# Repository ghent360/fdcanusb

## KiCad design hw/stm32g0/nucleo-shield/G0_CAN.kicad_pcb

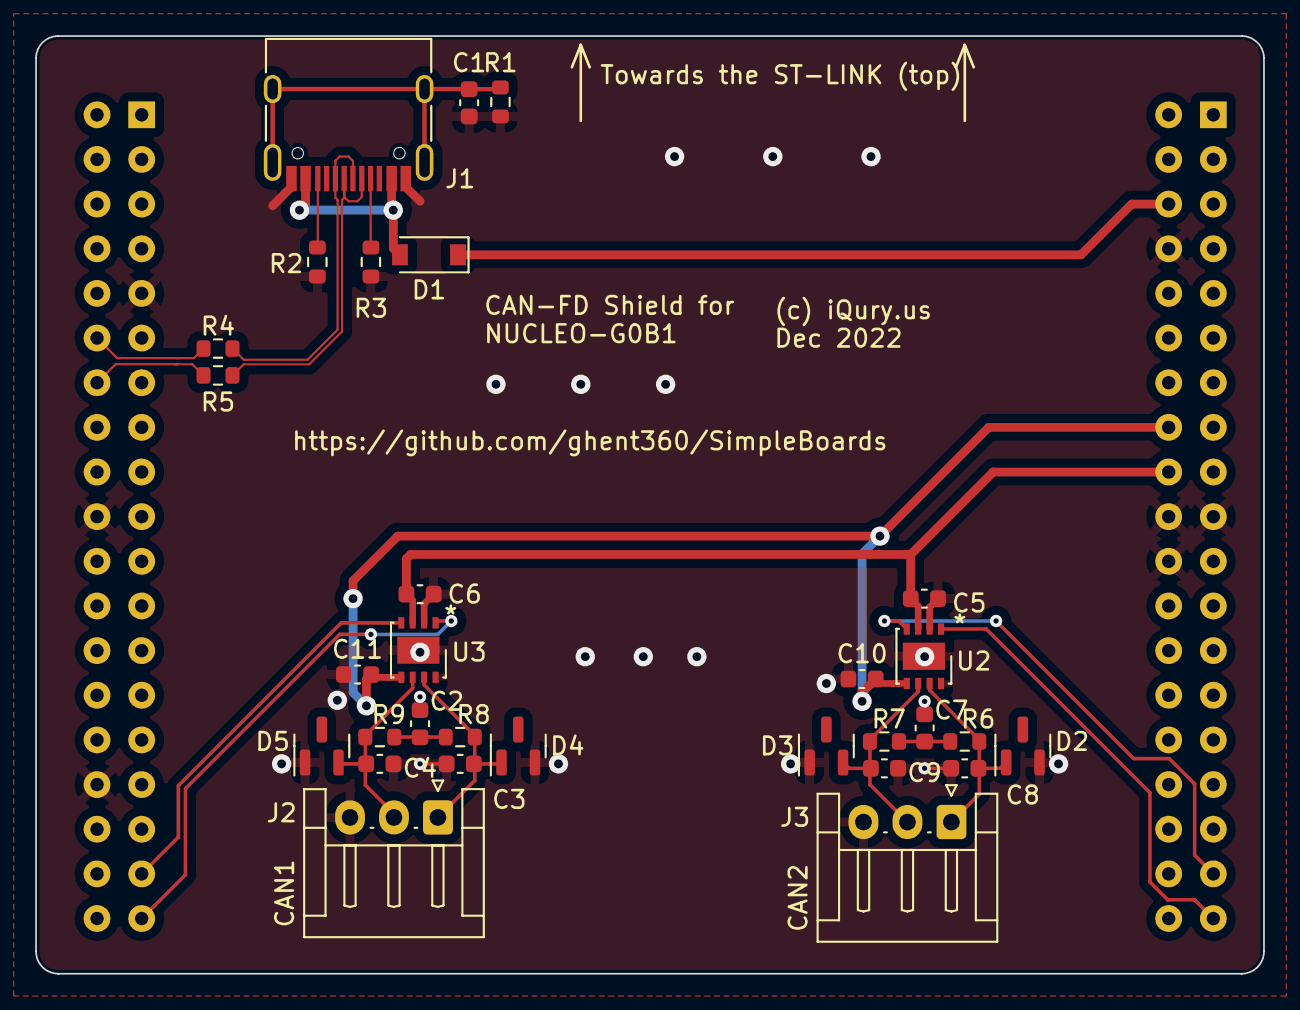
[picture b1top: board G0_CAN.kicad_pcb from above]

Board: 2 copper layers, 69.8 x 53.3 mm, 31 parts (1 on the bottom side), 22 nets.

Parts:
C1, C5, C6: 100nF; C_0603_1608Metric
C2, C7: 4700pF; C_0603_1608Metric
C3, C4, C8, C9: 47pF; C_0603_1608Metric
C10, C11: 10nF; C_0603_1608Metric
D1: B5819W; D_SOD-123
D2, D3, D4, D5: MMBZ27VC; SOT-23
J1: USB_C_Receptacle_USB2.0; USB_C_Receptacle_HRO_TYPE-C-31-M-12
J2: CAN1; JST_EH_S3B-EH_1x03_P2.50mm_Horizontal
J3: CAN2; JST_EH_S3B-EH_1x03_P2.50mm_Horizontal
R1: 100k; R_0603_1608Metric
R2, R3: 5.1k; R_0603_1608Metric
R4, R5: 22; R_0603_1608Metric
R6, R7, R8, R9: 60.4; R_0603_1608Metric
U1: Nucleo-64-G0B1; Nucleo-64
U2, U3: TJA1051TK-3; DFN-8-1EP_3x3mm_P0.65mm_EP1.55x2.4mm

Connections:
/3.3V: C10.2, C11.2, U1.16 (3.3v), U2.5 (VIO), U3.5 (VIO)
/5V: C5.1, C6.1, U1.18 (5V), U2.3 (VCC), U3.3 (VCC)
/CAN1_H: C3.1, D4.1 (K), J2.1, R8.1, U3.7 (CANH)
/CAN1_L: C4.2, D5.2 (K), J2.2, R9.2, U3.6 (CANL)
/CAN1_RX: U1.73 (PC4), U3.4 (RXD)
/CAN1_TX: U1.75 (PC5), U3.1 (TXD)
/CAN2_H: C8.1, D2.1 (K), J3.1, R6.1, U2.7 (CANH)
/CAN2_L: C9.2, D3.2 (K), J3.2, R7.2, U2.6 (CANL)
/CAN2_RX: U1.35 (PC2), U2.4 (RXD)
/CAN2_TX: U1.37 (PC3), U2.1 (TXD)
/D+: J1.A6 (D+), J1.B6 (D+), R4.1
/D-: J1.A7 (D-), J1.B7 (D-), R5.1
/E5V: D1.1 (K), U1.6 (E5V)
/USB_DN: R5.2, U1.52 (PA11)
/USB_DP: R4.2, U1.50 (PA12)
GND: C1.2, C2.2, C3.2, C4.1, C5.2, C6.2, C7.2, C8.2, C9.1, C10.1, C11.1, D2.2 (K), D3.1 (K), D4.2 (K), D5.1 (K), J1.A1 (GND), J1.A12 (GND), J1.B1 (GND), J1.B12 (GND), J2.3, J3.3, R1.2, R2.1, R3.1, U1.8 (GND), U1.19 (GND), U1.20 (GND), U1.22 (GND), U1.47 (GND), U1.58 (GND), U1.70 (AGND), U2.2 (GND), U2.8 (S), U2.9 (GND), U3.2 (GND), U3.8 (S), U3.9 (GND)
unnamed: C2.1, R8.2, R9.1
unnamed: C7.1, R6.2, R7.1
unnamed: D1.2 (A), J1.A4 (VBUS), J1.A9 (VBUS), J1.B4 (VBUS), J1.B9 (VBUS)
unnamed: J1.A5 (CC1), R3.2
unnamed: J1.B5 (CC2), R2.2
unnamed: C1.1, J1.S1 (SHIELD), R1.1

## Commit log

2023-01-28 Update libusb code.
2023-01-28 Fix build issue with the new libusb code.
2023-01-28 Use the usbd G4 driver from libusb. Add usb_startup code after clock init.
2023-01-28 Update bazel version. Fix build error. Fix warning.
2023-01-28 Update mbed repo version. Update mjlib repo version. Fix build errors.
2023-01-28 Switch for ghent360 mbed rules repo and try mbed 6.16.0
2023-01-28 Switch to G0 platform.
2023-03-27 Progress towards the STM32G0 port. Serial USB shows up.
2023-03-27 Fix clocks, still not quite working.
2023-04-01 Working on G0.
2023-04-01 Add hardware schematics. Only CAN1 port works with the fdcanusb software.
2023-10-19 Updete mbed repository to the correct commit.
